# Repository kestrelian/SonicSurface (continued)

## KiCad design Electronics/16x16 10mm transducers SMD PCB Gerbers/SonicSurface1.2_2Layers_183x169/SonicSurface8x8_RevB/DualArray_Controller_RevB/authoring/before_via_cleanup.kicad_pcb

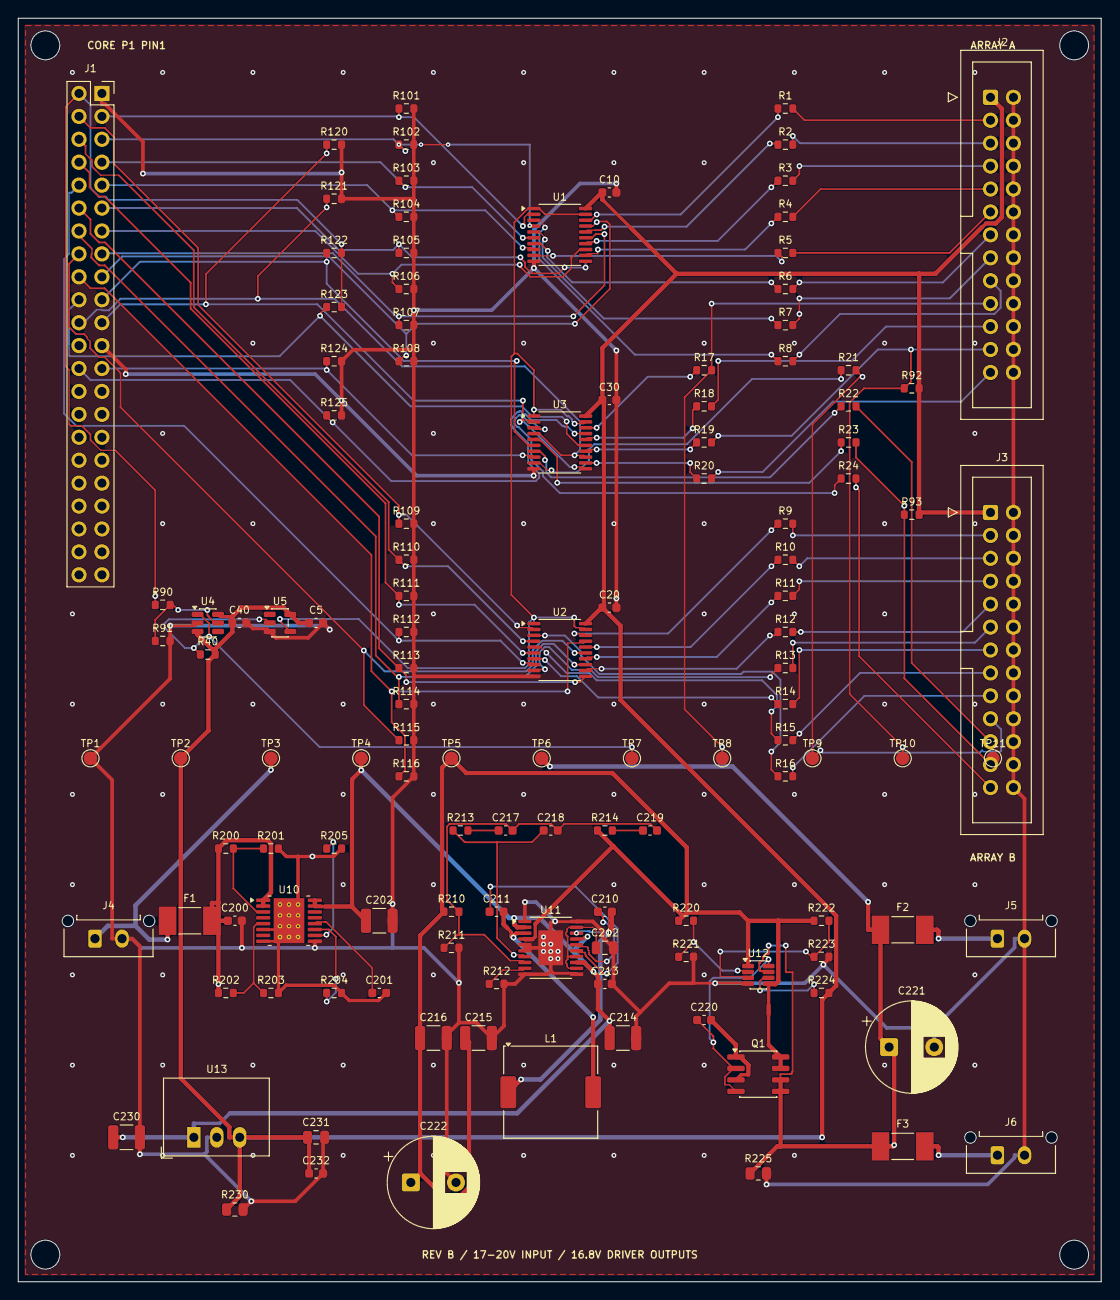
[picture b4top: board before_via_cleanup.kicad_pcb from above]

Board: 2 copper layers, 120.0 x 140.0 mm, 128 parts (0 on the bottom side), 104 nets.

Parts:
C5, C10, C20, C30, C40, C200, C201, C210, C211, C213, C232: 100nF 50V X7R; C_0603_1608Metric
C202, C214, C230: 10uF 50V X7R; C_1210_3225Metric
C212: 4.7uF 10V X7R; C_0805_2012Metric
C215, C216: 22uF 50V X7R; C_1210_3225Metric
C217: 8.2nF C0G; C_0603_1608Metric
C218: 150pF C0G; C_0603_1608Metric
C219: 1nF C0G; C_0603_1608Metric
C220: 47nF 50V X7R; C_0603_1608Metric
C221, C222: 470uF 35V low ESR; CP_Radial_D10.0mm_P5.00mm
C231: 10uF 10V X7R; C_0805_2012Metric
F1: 0451002.MRL / 2A 125V; Fuse_Littelfuse-NANO2-451_453
F2, F3: 0451.750MRL / 750mA 125V; Fuse_Littelfuse-NANO2-451_453
H1, H2, H3, H4: MountingHole_3.2mm_M3
J1: CoreEP4CE6 P1 / POWER PINS ISOLATED; PinSocket_2x22_P2.54mm_Vertical
J2: KEYED IDC26 / ARRAY A; IDC-Header_2x13_P2.54mm_Vertical
J3: KEYED IDC26 / ARRAY B; IDC-Header_2x13_P2.54mm_Vertical
J4: 17-20V DC INPUT; FP_910b6471cdf1
J5: 16.8V POWER ARRAY A; FP_910b6471cdf1
J6: 16.8V POWER ARRAY B; FP_910b6471cdf1
L1: 15uH MSS1048-153MLB; L_Coilcraft_MSS1048-XXX
Q1: Si9945CDY-T1-GE3; SOIC-8_3.9x4.9mm_P1.27mm
R1, R2, R3, R4, R5, R6, R7, R8, R9, R10, R11, R12, R13, R14, R15, R16, R17, R18, R19, R20, R21, R22, R23, R24: 33R source; R_0603_1608Metric
R40, R92, R93, R205, R224: 10k; R_0603_1608Metric
R90: 64.9k 0.1%; R_0603_1608Metric
R91, R201, R203, R211, R221: 10k 0.1%; R_0603_1608Metric
R101, R102, R103, R104, R105, R106, R107, R108, R109, R110, R111, R112, R113, R114, R115, R116, R120, R121, R122, R123, R124, R125: 100k; R_0603_1608Metric
R200: 121k 0.1%; R_0603_1608Metric
R202: 178k 0.1%; R_0603_1608Metric
R204: 8.06k 1%; R_0603_1608Metric
R210: 158k 0.1%; R_0603_1608Metric
R212: 47.5k 1%; R_0603_1608Metric
R213: 18k 1%; R_0603_1608Metric
R214: 2.67k 1%; R_0603_1608Metric
R220: 290k 0.1%; R_0603_1608Metric
R222: 340k 0.01%; R_0603_1608Metric
R223: 10k 0.01%; R_0603_1608Metric
R225: 10k 0.25W; R_0805_2012Metric
R230: 330R 0.125W minimum load; R_0805_2012Metric
TP1: GND; TestPoint_Pad_D1.5mm
TP2: +3V3; TestPoint_Pad_D1.5mm
TP3: VIN; TestPoint_Pad_D1.5mm
TP4: VPROT; TestPoint_Pad_D1.5mm
TP5: VREG_16V8; TestPoint_Pad_D1.5mm
TP6: VDRV_SAFE; TestPoint_Pad_D1.5mm
TP7: CORE_OK; TestPoint_Pad_D1.5mm
TP8: A_SCLK; TestPoint_Pad_D1.5mm
TP9: B_SCLK; TestPoint_Pad_D1.5mm
TP10: A_OE_N; TestPoint_Pad_D1.5mm
TP11: B_OE_N; TestPoint_Pad_D1.5mm
U1, U2, U3: SN74LVC244APW / Ioff; TSSOP-20_4.4x6.5mm_P0.65mm
U4: TPS3808G01DBVR; SOT-23-6
U5: SN74LVC1G04DBVR; SOT-23-5
U10: TPS26600PWPR; FP_eae3e738c928
U11: LTC3115IFE-1#PBF; FP_e5b083f4a3ae
U12: LTC4365ITS8#PBF; TSOT-23-8
U13: R-78E3.3-0.5; Converter_DCDC_RECOM_R-78E-0.5_THT

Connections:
+3V3: C5.1, C10.1, C20.1, C30.1, C40.1, C231.1, C232.1, J2.1, J3.1, R40.2, R92.2, R93.2, R224.2, R230.1, TP2.1, U1.20, U2.20, U3.20, U4.3, U4.6, U5.5, U13.3
A_CLR_N: J2.25, R20.2
A_CLR_N_BUF: R20.1, U3.12
A_CLR_N_SRC: J1.25, R124.1, U3.8
A_DATA0: J2.3, R1.2
A_DATA0_BUF: R1.1, U1.18
A_DATA0_SRC: J1.3, R101.1, U1.2
A_DATA1: J2.5, R2.2
A_DATA1_BUF: R2.1, U1.16
A_DATA1_SRC: J1.5, R102.1, U1.4
A_DATA2: J2.7, R3.2
A_DATA2_BUF: R3.1, U1.14
A_DATA2_SRC: J1.7, R103.1, U1.6
A_DATA3: J2.9, R4.2
A_DATA3_BUF: R4.1, U1.12
A_DATA3_SRC: J1.9, R104.1, U1.8
A_DATA4: J2.11, R5.2
A_DATA4_BUF: R5.1, U1.9
A_DATA4_SRC: J1.11, R105.1, U1.11
A_DATA5: J2.13, R6.2
A_DATA5_BUF: R6.1, U1.7
A_DATA5_SRC: J1.13, R106.1, U1.13
A_DATA6: J2.15, R7.2
A_DATA6_BUF: R7.1, U1.5
A_DATA6_SRC: J1.15, R107.1, U1.15
A_DATA7: J2.17, R8.2
A_DATA7_BUF: R8.1, U1.3
A_DATA7_SRC: J1.17, R108.1, U1.17
A_LATCH: J2.21, R18.2
A_LATCH_BUF: R18.1, U3.16
A_OE_N: J2.23, R19.2, R92.1, TP10.1
A_OE_N_BUF: R19.1, U3.14
A_OE_N_SRC: J1.19, R122.1, U3.6
A_SCLK: J2.19, R17.2, TP8.1
A_SCLK_BUF: R17.1, U3.18
BST1: C210.1, U11.16
BST2: C211.1, U11.15
B_CLR_N: J3.25, R24.2
B_CLR_N_BUF: R24.1, U3.3
B_CLR_N_SRC: J1.26, R125.1, U3.17
B_DATA0: J3.3, R9.2
B_DATA0_BUF: R9.1, U2.18
B_DATA0_SRC: J1.4, R109.1, U2.2
B_DATA1: J3.5, R10.2
B_DATA1_BUF: R10.1, U2.16
B_DATA1_SRC: J1.6, R110.1, U2.4
B_DATA2: J3.7, R11.2
B_DATA2_BUF: R11.1, U2.14
B_DATA2_SRC: J1.8, R111.1, U2.6
B_DATA3: J3.9, R12.2
B_DATA3_BUF: R12.1, U2.12
B_DATA3_SRC: J1.10, R112.1, U2.8
B_DATA4: J3.11, R13.2
B_DATA4_BUF: R13.1, U2.9
B_DATA4_SRC: J1.12, R113.1, U2.11
B_DATA5: J3.13, R14.2
B_DATA5_BUF: R14.1, U2.7
B_DATA5_SRC: J1.14, R114.1, U2.13
B_DATA6: J3.15, R15.2
B_DATA6_BUF: R15.1, U2.5
B_DATA6_SRC: J1.16, R115.1, U2.15
B_DATA7: J3.17, R16.2
B_DATA7_BUF: R16.1, U2.3
B_DATA7_SRC: J1.18, R116.1, U2.17
B_LATCH: J3.21, R22.2
B_LATCH_BUF: R22.1, U3.7
B_OE_N: J3.23, R23.2, R93.1, TP11.1
B_OE_N_BUF: R23.1, U3.5
B_OE_N_SRC: J1.20, R123.1, U3.15
B_SCLK: J3.19, R21.2, TP9.1
B_SCLK_BUF: R21.1, U3.9
COMP: C217.1, R213.2
CORE_3V3_SENSE: J1.2, R90.1, R122.2, R123.2
CORE_BAD: U1.1, U1.19, U2.1, U2.19, U3.1, U3.19, U5.4
CORE_OK: R40.1, TP7.1, U4.1, U5.2
CORE_SENSE_DIV: R90.2, R91.1, U4.5
FB: C217.2, C218.2, C219.2, R210.2, R211.1, U11.8
FET_COMMON: C220.2, Q1.1, Q1.3
FF: C219.1, R214.2
GND: C5.2, C10.2, C20.2, C30.2, C40.2, C200.2, C202.2, C212.2, C213.2, C214.2, C215.2, C216.2, C221.2, C222.2, C230.2, C231.2, C232.2, J1.1, J1.23, J2.2, J2.4, J2.6, J2.8, J2.10, J2.12, J2.14, J2.16, J2.18, J2.20, J2.22, J2.24, J2.26, J3.2, J3.4, J3.6, J3.8, J3.10, J3.12, J3.14, J3.16, J3.18, J3.20, J3.22, J3.24, J3.26, J4.2, J5.2, J6.2, R91.2, R101.2, R102.2, R103.2, R104.2, R105.2, R106.2, R107.2, R108.2, R109.2, R110.2, R111.2, R112.2, R113.2, R114.2, R115.2, R116.2, R120.2, R121.2, R124.2, R125.2, R211.2, R212.2, R221.2, R223.2, R225.2, R230.2, TP1.1, U1.10, U2.10, U3.10, U4.2, U5.3, U10.9, U11.1, U11.5, U11.6, U11.10, U11.11, U11.20, U11.21, U12.4, U13.2
IN_DVDT: C201.1, U10.12
IN_ILIM: R204.1, U10.11
IN_IMON: R205.1, U10.10
IN_OV: R202.2, R203.1, U10.5
IN_RTN: C201.2, R201.2, R203.2, R204.2, R205.2, U10.6, U10.8, U10.17
IN_UV: R200.2, R201.1, U10.3
LATCH_SRC: J1.22, R121.1, U3.4, U3.13
OUT_FAULT_N: R224.1, U12.6
OUT_OV: R222.2, R223.1, U12.3
OUT_UV: R220.2, R221.1, U12.2
PASS_GATE: C220.1, Q1.2, Q1.4, U12.8
RT: R212.1, U11.9
SCLK_SRC: J1.21, R120.1, U3.2, U3.11
SW1: C210.2, L1.1, U11.18
SW2: C211.2, L1.2, U11.3
VC: C218.1, R213.1, U11.7
VCC_BB: C212.1, U11.12, U11.14, U11.19
VDRV_A: F2.2, J5.1
VDRV_B: F3.2, J6.1
VDRV_SAFE: C221.1, F2.1, F3.1, Q1.5, Q1.6, R225.1, TP6.1, U12.7
VIN: F1.1, J4.1, TP3.1
VINPUT_FUSED: C200.1, F1.2, R200.1, R202.1, U10.1, U10.2
VPROT: C202.1, C213.1, C214.1, C230.1, TP4.1, U10.15, U10.16, U11.2, U11.13, U11.17, U13.1
VREG_16V8: C215.1, C216.1, C222.1, Q1.7, Q1.8, R210.1, R214.1, R220.1, R222.1, TP5.1, U11.4, U12.1, U12.5
